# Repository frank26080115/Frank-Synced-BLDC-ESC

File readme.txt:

Frank's Sychronizable Brushless DC Motor ESC

== Oct 23, 2012 ==

Schematic and PCB are in CadSoft EAGLE 6.2 format
PNG preview images are also available
Gerber files are available

No hardware has been made yet, so nothing is tested
Component selection has not been done yet

Still a work in progress

Source code is a modified version of SimonK's ESC code

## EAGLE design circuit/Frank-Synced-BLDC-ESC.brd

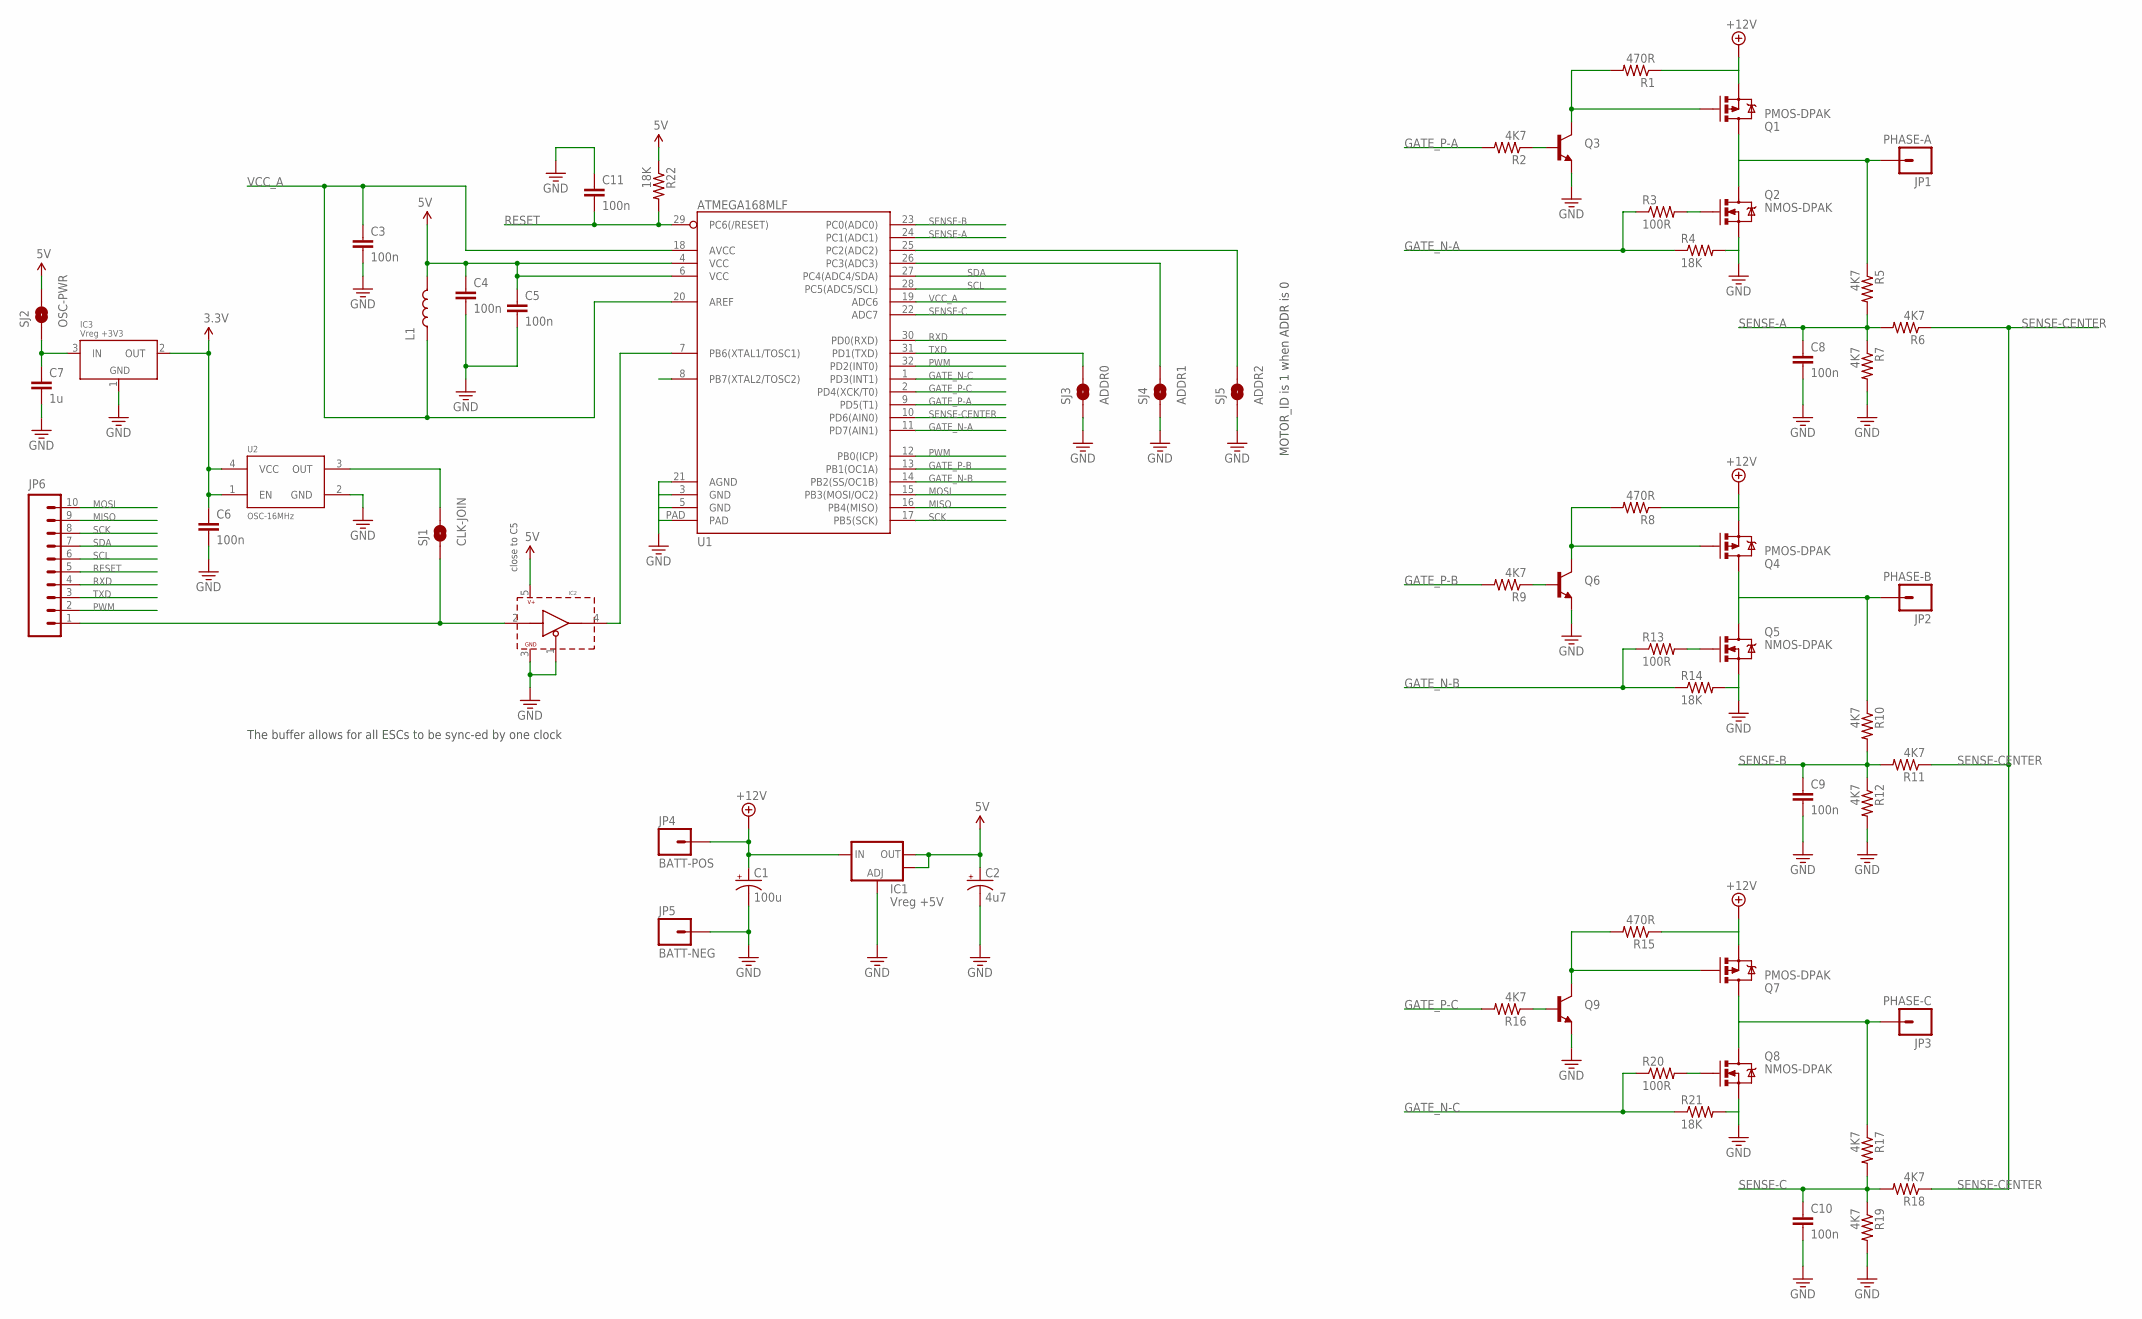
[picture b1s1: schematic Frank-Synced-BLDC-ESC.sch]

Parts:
C1: 100u; CAP-AXIAL-LARGE
C2: 4u7; EIA3216-KIT
C3, C4, C5, C6, C8, C9, C10, C11: 100n; 0603-CAP
C7: 1u; 0603-CAP
IC1: Vreg +5V; SOT223
IC2: BUFFER-SINGLE-SOT-23-5; SOT23-5
IC3: Vreg +3V3; SOT23-3
JP1: PHASE-A; 1X1-MOTOR
JP2: PHASE-B; 1X1-MOTOR
JP3: PHASE-C; 1X1-MOTOR
JP4: BATT-POS; 1X1-BATT
JP5: BATT-NEG; 1X1-BATT
JP6: M10"; 1X10
L1: INDUCTOR0603; 0603
Q1, Q4, Q7: PMOS-DPAK; DPAK
Q2, Q5, Q8: NMOS-DPAK; DPAK
Q3, Q6, Q9: TRANSISTOR_NPNSOT23-3; SOT23-3
R1, R8, R15: 470R; 0603-RES
R2, R5, R6, R7, R9, R10, R11, R12, R16, R17, R18, R19: 4K7; 0603-RES
R3, R13, R20: 100R; 0603-RES
R4, R14, R21, R22: 18K; 0603-RES
SJ1: CLK-JOIN; SJ_2S
SJ2: OSC-PWR; SJ_2S
SJ3: ADDR0; SJ_2S-NO
SJ4: ADDR1; SJ_2S-NO
SJ5: ADDR2; SJ_2S-NO
U1: ATMEGA168MLF; MLF32
U2: OSC-16MHz; OSCILLATOR-2.5X2

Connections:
3.3V: C6.1, IC3.2 (OUT), U2.1 (EN), U2.4 (VCC)
5V: C2.A (+), C4.1, C5.1, IC1.2 (OUT), IC1.4 (OUT), IC2.5 (V+), L1.2, R22.1, SJ2.2, U1.4 (VCC), U1.6 (VCC)
+12V: C1.+, IC1.3 (IN), JP4.P$1, Q1.3 (S), Q4.3 (S), Q7.3 (S), R1.1, R8.1, R15.1
CLK: IC2.4 (OUT), U1.7 (PB6(XTAL1/TOSC1))
GATE_N-A: R3.1, R4.1, U1.11 (PD7(AIN1))
GATE_N-B: R13.1, R14.1, U1.14 (PB2(SS/OC1B))
GATE_N-C: R20.1, R21.1, U1.1 (PD3(INT1))
GATE_P-A: R2.2, U1.9 (PD5(T1))
GATE_P-B: R9.2, U1.13 (PB1(OC1A))
GATE_P-C: R16.2, U1.2 (PD4(XCK/T0))
GND: C1.-, C2.C (-), C3.2, C4.2, C5.2, C6.2, C7.2, C8.2, C9.2, C10.2, C11.1, IC1.1 (ADJ), IC2.1 (!OE), IC2.3 (GND), IC3.1 (GND), JP5.P$1, Q2.3 (S), Q3.2 (E), Q5.3 (S), Q6.2 (E), Q8.3 (S), Q9.2 (E), R4.2, R7.2, R12.2, R14.2, R19.2, R21.2, SJ3.1, SJ4.1, SJ5.1, U1.3 (GND), U1.5 (GND), U1.21 (AGND), U1.PAD, U2.2 (GND)
MISO: JP6.9, U1.16 (PB4(MISO))
MOSI: JP6.10, U1.15 (PB3(MOSI/OC2))
unnamed: JP1.P$1, Q1.4 (D), Q2.4 (D), R5.1
unnamed: Q3.1 (B), R2.1
unnamed: Q1.1 (G), Q3.3 (C), R1.2
unnamed: SJ4.2, U1.26 (PC3(ADC3))
unnamed: SJ5.2, U1.25 (PC2(ADC2))
unnamed: Q2.1 (G), R3.2
unnamed: JP2.P$1, Q4.4 (D), Q5.4 (D), R10.1
unnamed: C7.1, IC3.3 (IN), SJ2.1
unnamed: Q4.1 (G), Q6.3 (C), R8.2
unnamed: Q6.1 (B), R9.1
unnamed: Q5.1 (G), R13.2
unnamed: JP3.P$1, Q7.4 (D), Q8.4 (D), R17.1
unnamed: Q7.1 (G), Q9.3 (C), R15.2
unnamed: Q9.1 (B), R16.1
unnamed: Q8.1 (G), R20.2
unnamed: IC2.2 (IN), JP6.1, SJ1.1
unnamed: SJ1.2, U2.3 (OUT)
PWM: JP6.2, U1.12 (PB0(ICP)), U1.32 (PD2(INT0))
RESET: C11.2, JP6.5, R22.2, U1.29 (PC6(/RESET))
RXD: JP6.4, U1.30 (PD0(RXD))
SCK: JP6.8, U1.17 (PB5(SCK))
SCL: JP6.6, U1.28 (PC5(ADC5/SCL))
SDA: JP6.7, U1.27 (PC4(ADC4/SDA))
SENSE-A: C8.1, R5.2, R6.2, R7.1, U1.24 (PC1(ADC1))
SENSE-B: C9.1, R10.2, R11.2, R12.1, U1.23 (PC0(ADC0))
SENSE-C: C10.1, R17.2, R18.2, R19.1, U1.22 (ADC7)
SENSE-CENTER: R6.1, R11.1, R18.1, U1.10 (PD6(AIN0))
TXD: JP6.3, SJ3.2, U1.31 (PD1(TXD))
VCC_A: C3.1, L1.1, U1.18 (AVCC), U1.19 (ADC6), U1.20 (AREF)

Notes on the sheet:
MOTOR_ID is 1 when ADDR is 0
The buffer allows for all ESCs to be sync-ed by one clock
close to C5

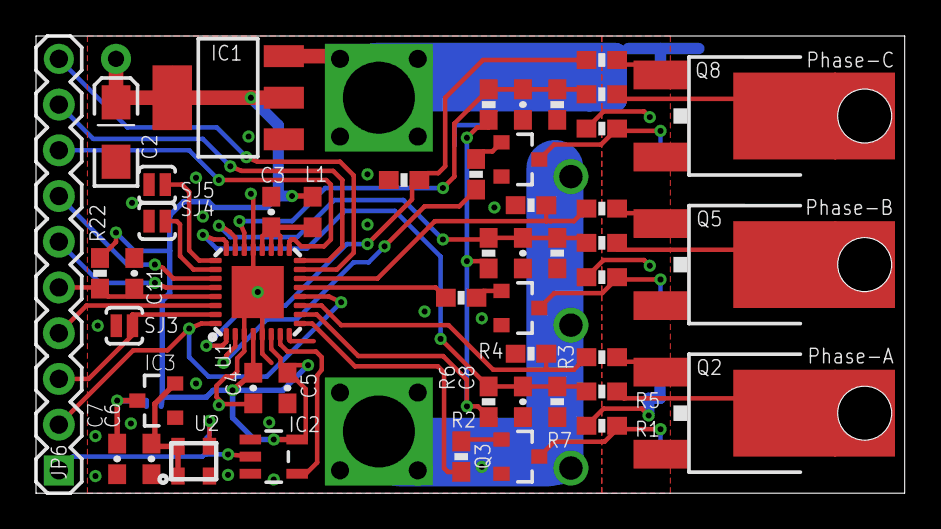
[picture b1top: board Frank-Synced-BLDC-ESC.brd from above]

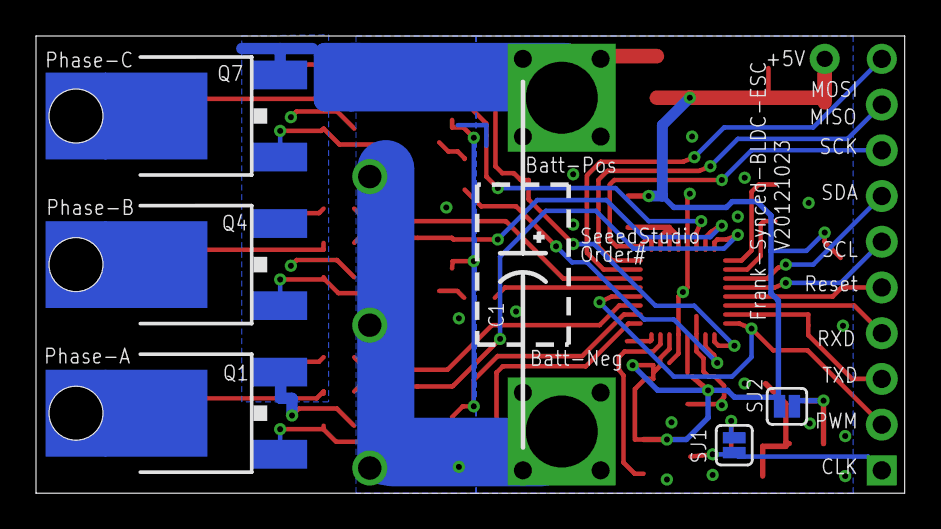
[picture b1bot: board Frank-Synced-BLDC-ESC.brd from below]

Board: 2 copper layers, 48.3 x 25.4 mm, 59 parts (11 on the bottom side), 42 nets.

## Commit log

2012-10-23 some more fine tunin' traces
2012-10-23 just a bit more shorter, 1.9" now
2012-10-23 update preview pictures
2012-10-23 minor changes to motor phase connection, added some information text
2012-10-25 layout for 7 x 5 mm 5V oscillator
2012-10-25 branch uses 2.5 x 2 mm sized +3.3V powered oscillator instead
2012-10-26 gerber files for this branch
